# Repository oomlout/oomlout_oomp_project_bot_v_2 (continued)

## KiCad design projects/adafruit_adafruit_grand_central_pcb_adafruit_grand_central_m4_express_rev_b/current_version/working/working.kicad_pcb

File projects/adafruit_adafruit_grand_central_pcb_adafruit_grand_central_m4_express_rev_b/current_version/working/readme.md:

# adafruit_grand_central_pcb
 
## summary 
* id: adafruit_adafruit_grand_central_pcb_adafruit_grand_central_m4_express_rev_b
* user: adafruit
* name: adafruit_grand_central_pcb
* board: adafruit_grand_central_m4_express_rev_b
* repo: https://github.com/adafruit/Adafruit-Grand-Central-PCB

* src_file_repo_sch: 
* src_file_repo_sch_link: https://github.com/adafruit/Adafruit-Grand-Central-PCB/tree/master/
* full details link: https://github.com/oomlout/oomlout_oomp_project_bot_v_2/tree/main/projects/adafruit_adafruit_grand_central_pcb_adafruit_grand_central_m4_express_rev_b/current_version/working  

## schematic  
  
[schematic (pdf)](working_schematic.pdf) 

## pcb  

[board (pdf)](working.pdf)  

## bom_schematic
| Ref | Qnty | Value | Cmp name | Footprint | Description | Vendor | DNP | 
| --- | --- | --- | --- | --- | --- | --- | --- | 
| ANALOGH0 | 1 | 20610 | HEADER-1X8OVALWAVE | working:1X08_OVALWAVE |  |  |  | 
| ANALOGL0 | 1 | 20610 | HEADER-1X8OVALWAVE | working:1X08_OVALWAVE |  |  |  | 
| C1, C2, C3 | 3 | 10uF | CAP_CERAMIC0805-NOOUTLINE | working:0805-NO |  |  |  | 
| C4, C6, C8, C10, C11, C14, C15, C16, C18, C19, C20, C21, C22, C23, C24, C25 | 16 | .1u | CAP_CERAMIC0603_NO | working:0603-NO |  |  |  | 
| C5, C7 | 2 | 22pF | CAP_CERAMIC0603_NO | working:0603-NO |  |  |  | 
| C9 | 1 | 1uF | CAP_CERAMIC0603_NO | working:0603-NO |  |  |  | 
| C12, C13, C17 | 3 | 0.1uF | CAP_CERAMIC0603_NO | working:0603-NO |  |  |  | 
| D1 | 1 | MBR120 | DIODE-SCHOTTKYSOD-123 | working:SOD-123 |  |  |  | 
| F2 | 1 | 500mA | PTCFUSE-1206 | working:R1206 |  |  |  | 
| FB2 | 1 | FERRITE | FERRITE-0805NO | working:0805-NO |  |  |  | 
| FD1, FD2, FD3, FD4, FD5 | 5 | FIDUCIAL_1MM | FIDUCIAL_1MM | working:FIDUCIAL_1MM |  |  |  | 
| GROUND1 | 1 | SOLDERJUMPERCLOSED | SOLDERJUMPERCLOSED | working:SOLDERJUMPER_CLOSEDWIRE |  |  |  | 
| IC3 | 1 | 741G125DBV | 741G125DBV | working:SOT23-5 |  |  |  | 
| ICSP0 | 1 | 3x2 M | HEADER-2X3 | working:2X03_ROUND_70MIL |  |  |  | 
| IOH0 | 1 | 20611 | HEADER-1X10OVALWAVE | working:1X10_OVALWAVE |  |  |  | 
| IOL0 | 1 | 20610 | HEADER-1X8OVALWAVE | working:1X08_OVALWAVE |  |  |  | 
| JP1 | 1 | HEADER-1X1ROUND | HEADER-1X1ROUND | working:1X01_ROUND |  |  |  | 
| JP2 | 1 | PINHD-2X18_THICKWAV | PINHD-2X18_THICKWAV | working:2X18_THICKWAVE |  |  |  | 
| L0 | 1 | RED | LED0805_NOOUTLINE | working:CHIPLED_0805_NOOUTLINE |  |  |  | 
| L1 | 1 | 10uH | INDUCTOR | working:INDUCTOR_1007 |  |  |  | 
| LED1 | 1 | WS2812B3535 | WS2812B3535 | working:LED3535 |  |  |  | 
| ON0 | 1 | GREEN | LED0805_NOOUTLINE | working:CHIPLED_0805_NOOUTLINE |  |  |  | 
| PC1 | 1 | 47uF/25V | CAP_ELECTROLYTICPANASONIC_D | working:PANASONIC_D |  |  |  | 
| PC2 | 1 | 47uF+/6.3V+ | CAP_ELECTROLYTICPANASONIC_D | working:PANASONIC_D |  |  |  | 
| POWER0 | 1 | 20610 | HEADER-1X8OVALWAVE | working:1X08_OVALWAVE |  |  |  | 
| R1 | 1 | 100K | RESISTOR_4PACK | working:RESPACK_4X0603 |  |  |  | 
| R2 | 1 | 1K | RESISTOR_4PACK | working:RESPACK_4X0603 |  |  |  | 
| R3, R5, R7 | 3 | 10K | RESISTOR_0603_NOOUT | working:0603-NO |  |  |  | 
| R4 | 1 | 1K | RESISTOR_0603_NOOUT | working:0603-NO |  |  |  | 
| R11 | 1 | 330R | RESISTOR_0603_NOOUT | working:0603-NO |  |  |  | 
| RESET0 | 1 | EVQQ 6mm | SWITCH_TACT_SMT_EVQQ2_SMALL | working:EVQ-Q2_SMALLER |  |  |  | 
| RXLED0 | 1 | YELLOW | LED0805_NOOUTLINE | working:CHIPLED_0805_NOOUTLINE |  |  |  | 
| SJ1 | 1 | AREF_3V | SOLDERJUMPERCLOSED | working:SOLDERJUMPER_CLOSEDWIRE |  |  |  | 
| SW1 | 1 | SWITCH_SPDT | SWITCH_SPDT | working:SPDT_SMT_SSSS811101 |  |  |  | 
| T2 | 1 | DMP3098L-7 | PMOSSOT23 | working:SOT-23 |  |  |  | 
| TR1 | 1 | DMP3098L-7 | 0297_PMV48XP | working:SOT-23 |  |  |  | 
| TXLED0 | 1 | YELLOW | LED0805_NOOUTLINE | working:CHIPLED_0805_NOOUTLINE |  |  |  | 
| U1 | 1 | NCP1117ST50T3G | LM1117SOT223-REFLOW | working:SOT223-R |  |  |  | 
| U2 | 1 | LP2985-XXDBVR | LP2985-XXDBVR | working:SOT23-DBV |  |  |  | 
| U3 | 1 | GD25Q64 | SPIFLASH_SOIC8208MIL | working:SOIC8_208MIL |  |  |  | 
| U$1 | 1 | SAMD51PXXA | SAMD51PXXA | working:SQFP-S-14X14-128 |  |  |  | 
| UART0 | 1 | 20610 | HEADER-1X8OVALWAVE | working:1X08_OVALWAVE |  |  |  | 
| X1 | 1 | microsd | MICROSD | working:MICROSD |  |  |  | 
| X2 | 1 | 2x5 0.05" SWD | JTAG-CORTEXBOXPOSTS | working:2X05_1.27MM_BOX_POSTS |  |  |  | 
| X3 | 1 | USB_W_SHIELD_V2 | USB_W_SHIELD_V2 | working:4UCONN_20329_V2 |  |  |  | 
| X4 | 1 | 32.768 | XTAL-3.2X1.5 | working:XTAL3215 |  |  |  | 
| X5 | 1 | 2.1mm | DCBARRELPTH | working:DCJACK_2MM_PTH |  |  |  |

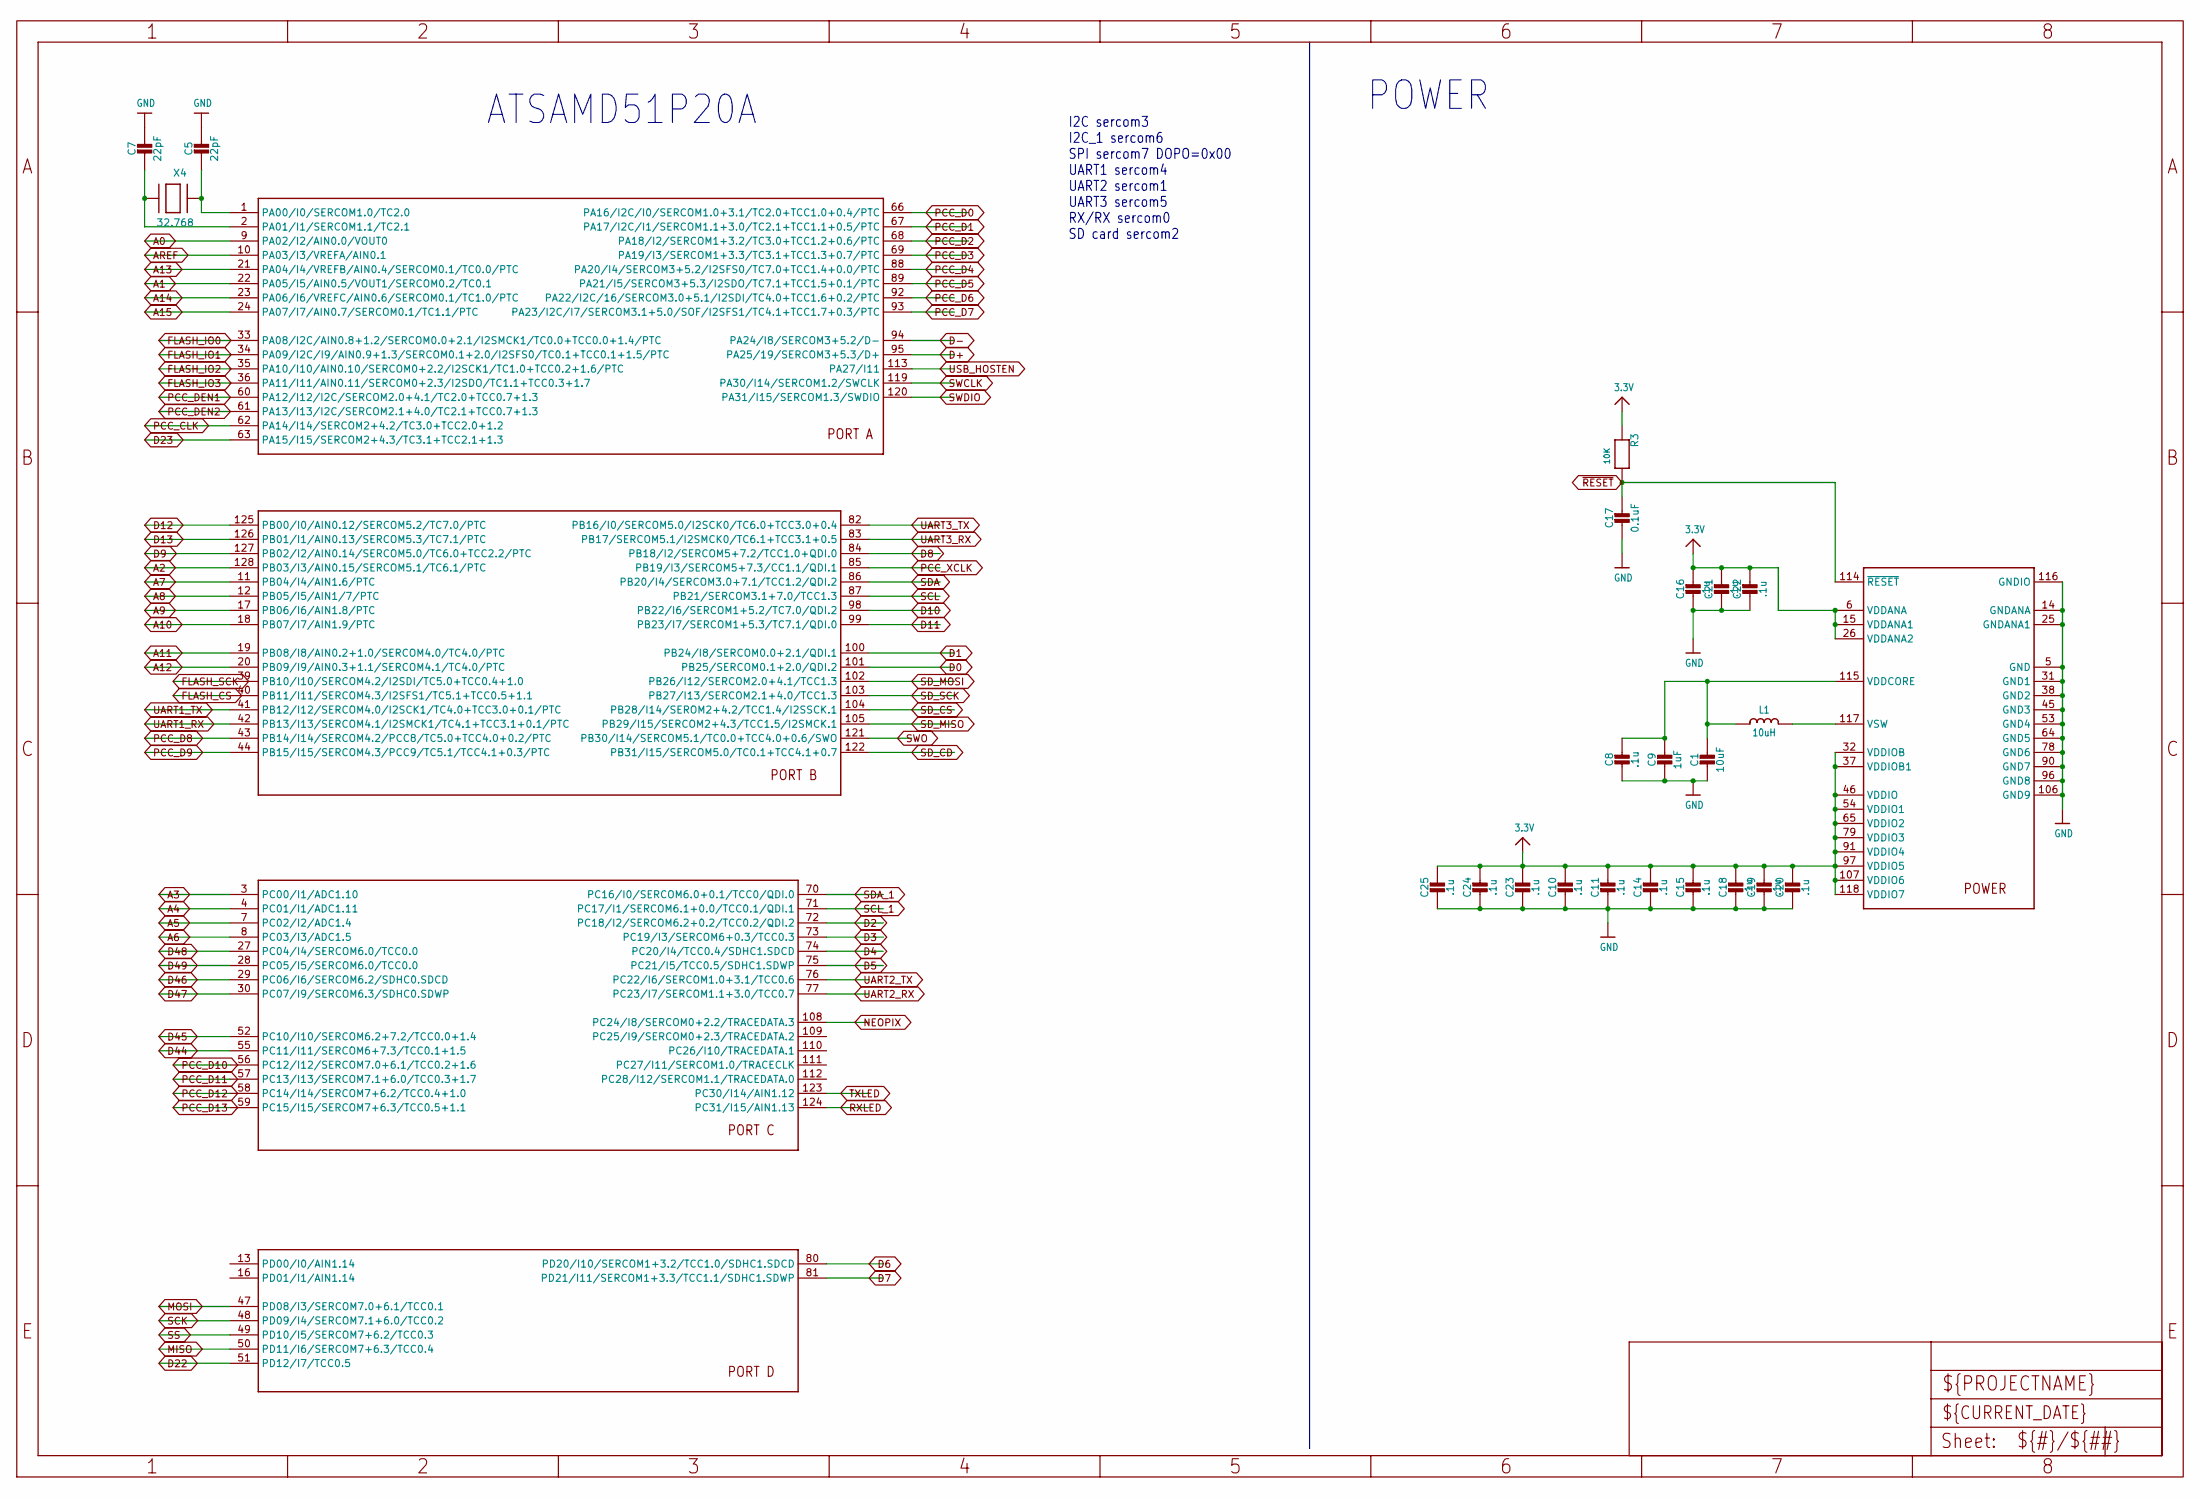
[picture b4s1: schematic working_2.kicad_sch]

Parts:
C1: 10uF; 0805-NO
C5, C7: 22pF; 0603-NO
C8, C10, C11, C14, C15, C16, C18, C19, C20, C21, C22, C23, C24, C25: .1u; 0603-NO
C9: 1uF; 0603-NO
C17: 0.1uF; 0603-NO
L1: 10uH; INDUCTOR_1007
R3: 10K; 0603-NO
U$1: SAMD51PXXA; SQFP-S-14X14-128
X4: 32.768; XTAL3215

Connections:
3.3V: C10.2, C11.2, C14.2, C15.2, C16.2, C18.2, C19.2, C20.2, C21.2, C22.2, C23.2, C24.2, C25.2, R3.1, U$1.6 (VDDANA), U$1.15 (VDDANA1), U$1.26 (VDDANA2), U$1.32 (VDDIOB), U$1.37 (VDDIOB1), U$1.46 (VDDIO), U$1.54 (VDDIO1), U$1.65 (VDDIO2), U$1.79 (VDDIO3), U$1.91 (VDDIO4), U$1.97 (VDDIO5), U$1.107 (VDDIO6), U$1.118 (VDDIO7); also elsewhere on the board
A0: U$1.9 (PA02/I2/AIN0.0/VOUT0); also elsewhere on the board
A1: U$1.22 (PA05/I5/AIN0.5/VOUT1/SERCOM0.2/TC0.1); also elsewhere on the board
A2: U$1.128 (PB03/I3/AIN0.15/SERCOM5.1/TC6.1/PTC); also elsewhere on the board
A3: U$1.3 (PC00/I1/ADC1.10); also elsewhere on the board
A4: U$1.4 (PC01/I1/ADC1.11); also elsewhere on the board
A5: U$1.7 (PC02/I2/ADC1.4); also elsewhere on the board
A6: U$1.8 (PC03/I3/ADC1.5); also elsewhere on the board
A7: U$1.11 (PB04/I4/AIN1.6/PTC); also elsewhere on the board
A8: U$1.12 (PB05/I5/AIN1/7/PTC); also elsewhere on the board
A9: U$1.17 (PB06/I6/AIN1.8/PTC); also elsewhere on the board
A10: U$1.18 (PB07/I7/AIN1.9/PTC); also elsewhere on the board
A11: U$1.19 (PB08/I8/AIN0.2+1.0/SERCOM4.0/TC4.0/PTC); also elsewhere on the board
A12: U$1.20 (PB09/I9/AIN0.3+1.1/SERCOM4.1/TC4.0/PTC); also elsewhere on the board
A13: U$1.21 (PA04/I4/VREFB/AIN0.4/SERCOM0.1/TC0.0/PTC); also elsewhere on the board
A14: U$1.23 (PA06/I6/VREFC/AIN0.6/SERCOM0.1/TC1.0/PTC); also elsewhere on the board
A15: U$1.24 (PA07/I7/AIN0.7/SERCOM0.1/TC1.1/PTC); also elsewhere on the board
AREF: U$1.10 (PA03/I3/VREFA/AIN0.1); also elsewhere on the board
D0: U$1.101 (PB25/SERCOM0.1+2.0/QDI.2); also elsewhere on the board
D1: U$1.100 (PB24/I8/SERCOM0.0+2.1/QDI.1); also elsewhere on the board
D2: U$1.72 (PC18/I2/SERCOM6.2+0.2/TCC0.2/QDI.2); also elsewhere on the board
D3: U$1.73 (PC19/I3/SERCOM6+0.3/TCC0.3); also elsewhere on the board
D4: U$1.74 (PC20/I4/TCC0.4/SDHC1.SDCD); also elsewhere on the board
D5: U$1.75 (PC21/I5/TCC0.5/SDHC1.SDWP); also elsewhere on the board
D6: U$1.80 (PD20/I10/SERCOM1+3.2/TCC1.0/SDHC1.SDCD); also elsewhere on the board
D7: U$1.81 (PD21/I11/SERCOM1+3.3/TCC1.1/SDHC1.SDWP); also elsewhere on the board
D8: U$1.84 (PB18/I2/SERCOM5+7.2/TCC1.0+QDI.0); also elsewhere on the board
D9: U$1.127 (PB02/I2/AIN0.14/SERCOM5.0/TC6.0+TCC2.2/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); also elsewhere on the board
D10: U$1.98 (PB22/I6/SERCOM1+5.2/TC7.0/QDI.2); also elsewhere on the board
D11: U$1.99 (PB23/I7/SERCOM1+5.3/TC7.1/QDI.0); also elsewhere on the board
D12: U$1.125 (PB00/I0/AIN0.12/SERCOM5.2/TC7.0/PTC); also elsewhere on the board
D13: U$1.126 (PB01/I1/AIN0.13/SERCOM5.3/TC7.1/PTC); also elsewhere on the board
D22: U$1.51 (PD12/I7/TCC0.5); also elsewhere on the board
D23: U$1.63 (PA15/I15/SERCOM2+4.3/TC3.1+TCC2.1+1.3); also elsewhere on the board
D44: U$1.55 (PC11/I11/SERCOM6+7.3/TCC0.1+1.5); also elsewhere on the board
D45: U$1.52 (PC10/I10/SERCOM6.2+7.2/TCC0.0+1.4); also elsewhere on the board
D46: U$1.29 (PC06/I6/SERCOM6.2/SDHC0.SDCD); also elsewhere on the board
D47: U$1.30 (PC07/I9/SERCOM6.3/SDHC0.SDWP); also elsewhere on the board
D48: U$1.27 (PC04/I4/SERCOM6.0/TCC0.0); also elsewhere on the board
D49: U$1.28 (PC05/I5/SERCOM6.0/TCC0.0); also elsewhere on the board
D+: U$1.95 (PA25/19/SERCOM3+5.3/D+); also elsewhere on the board
D-: U$1.94 (PA24/I8/SERCOM3+5.2/D-); also elsewhere on the board
FLASH_CS: U$1.40 (PB11/I11/SERCOM4.3/I2SFS1/TC5.1+TCC0.5+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); also elsewhere on the board
FLASH_IO0: U$1.33 (PA08/I2C/AIN0.8+1.2/SERCOM0.0+2.1/I2SMC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); also elsewhere on the board
FLASH_IO1: U$1.34 (PA09/I2C/I9/AIN0.9+1.3/SERCOM0.1+2.0/I2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); also elsewhere on the board
FLASH_IO2: U$1.35 (PA10/I10/AIN0.10/SERCOM0+2.2/I2SCK1/TC1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); also elsewhere on the board
FLASH_IO3: U$1.36 (PA11/I11/AIN0.11/SERCOM0+2.3/I2SDO/TC1.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); also elsewhere on the board
FLASH_SCK: U$1.39 (PB10/I10/SERCOM4.2/I2SDI/TC5.0+TCC0.4+1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); also elsewhere on the board
GND: C1.2, C5.2, C7.2, C8.1, C9.2, C10.1, C11.1, C14.1, C15.1, C16.1, C17.1, C18.1, C19.1, C20.1, C21.1, C22.1, C23.1, C24.1, C25.1, U$1.5 (GND), U$1.14 (GNDANA), U$1.25 (GNDANA1), U$1.31 (GND1), U$1.38 (GND2), U$1.45 (GND3), U$1.53 (GND4), U$1.64 (GND5), U$1.78 (GND6), U$1.90 (GND7), U$1.96 (GND8), U$1.106 (GND9), U$1.116 (GNDIO); also elsewhere on the board
MISO: U$1.50 (PD11/I6/SERCOM7+6.3/TCC0.4); also elsewhere on the board
MOSI: U$1.47 (PD08/I3/SERCOM7.0+6.1/TCC0.1); also elsewhere on the board
unnamed: L1.P$2 (2), U$1.117 (VSW)
unnamed: C5.1, U$1.1 (PA00/I0/SERCOM1.0/TC2.0), X4.P$1
unnamed: C7.1, U$1.2 (PA01/I1/SERCOM1.1/TC2.1), X4.P$2
NEOPIX: U$1.108 (PC24/I8/SERCOM0+2.2/TRACEDATA.3); also elsewhere on the board
PCC_CLK: U$1.62 (PA14/I14/SERCOM2+4.2/TC3.0+TCC2.0+1.2); also elsewhere on the board
PCC_D0: U$1.66 (PA16/I2C/I0/SERCOM1.0+3.1/TC2.0+TCC1.0+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); also elsewhere on the board
PCC_D1: U$1.67 (PA17/I2C/I1/SERCOM1.1+3.0/TC2.1+TCC1.1+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); also elsewhere on the board
PCC_D2: U$1.68 (PA18/I2/SERCOM1+3.2/TC3.0+TCC1.2+0.6/PTC); also elsewhere on the board
PCC_D3: U$1.69 (PA19/I3/SERCOM1+3.3/TC3.1+TCC1.3+0.7/PTC); also elsewhere on the board
PCC_D4: U$1.88 (PA20/I4/SERCOM3+5.2/I2SFS0/TC7.0+TCC1.4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); also elsewhere on the board
PCC_D5: U$1.89 (PA21/I5/SERCOM3+5.3/I2SDO/TC7.1+TCC1.5+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); also elsewhere on the board
PCC_D6: U$1.92 (PA22/I2C/16/SERCOM3.0+5.1/I2SDI/TC4.0+T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); also elsewhere on the board
PCC_D7: U$1.93 (PA23/I2C/I7/SERCOM3.1+5.0/SOF/I2SFS1/TC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); also elsewhere on the board
PCC_D8: U$1.43 (PB14/I14/SERCOM4.2/PCC8/TC5.0+TCC4.0+0.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); also elsewhere on the board
PCC_D9: U$1.44 (PB15/I15/SERCOM4.3/PCC9/TC5.1/TCC4.1+0.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); also elsewhere on the board
PCC_D10: U$1.56 (PC12/I12/SERCOM7.0+6.1/TCC0.2+1.6); also elsewhere on the board
PCC_D11: U$1.57 (PC13/I13/SERCOM7.1+6.0/TCC0.3+1.7); also elsewhere on the board
PCC_D12: U$1.58 (PC14/I14/SERCOM7+6.2/TCC0.4+1.0); also elsewhere on the board
PCC_D13: U$1.59 (PC15/I15/SERCOM7+6.3/TCC0.5+1.1); also elsewhere on the board
PCC_DEN1: U$1.60 (PA12/I12/I2C/SERCOM2.0+4.1/TC2.0+TCC0.7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); also elsewhere on the board
PCC_DEN2: U$1.61 (PA13/I13/I2C/SERCOM2.1+4.0/TC2.1+TCC0.7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); also elsewhere on the board
PCC_XCLK: U$1.85 (PB19/I3/SERCOM5+7.3/CC1.1/QDI.1); also elsewhere on the board
RXLED: U$1.124 (PC31/I15/AIN1.13); also elsewhere on the board
SCK: U$1.48 (PD09/I4/SERCOM7.1+6.0/TCC0.2); also elsewhere on the board
SCL: U$1.87 (PB21/SERCOM3.1+7.0/TCC1.3); also elsewhere on the board
SCL_1: U$1.71 (PC17/I1/SERCOM6.1+0.0/TCC0.1/QDI.1); also elsewhere on the board
SDA: U$1.86 (PB20/I4/SERCOM3.0+7.1/TCC1.2/QDI.2); also elsewhere on the board
SDA_1: U$1.70 (PC16/I0/SERCOM6.0+0.1/TCC0/QDI.0); also elsewhere on the board
SD_CD: U$1.122 (PB31/I15/SERCOM5.0/TC0.1+TCC4.1+0.7); also elsewhere on the board
SD_CS: U$1.104 (PB28/I14/SEROM2+4.2/TCC1.4/I2SSCK.1); also elsewhere on the board
SD_MISO: U$1.105 (PB29/I15/SERCOM2+4.3/TCC1.5/I2SMCK.1); also elsewhere on the board
SD_MOSI: U$1.102 (PB26/I12/SERCOM2.0+4.1/TCC1.3); also elsewhere on the board
SD_SCK: U$1.103 (PB27/I13/SERCOM2.1+4.0/TCC1.3); also elsewhere on the board
SS: U$1.49 (PD10/I5/SERCOM7+6.2/TCC0.3); also elsewhere on the board
SWCLK: U$1.119 (PA30/I14/SERCOM1.2/SWCLK); also elsewhere on the board
SWDIO: U$1.120 (PA31/I15/SERCOM1.3/SWDIO); also elsewhere on the board
SWO: U$1.121 (PB30/I14/SERCOM5.1/TC0.0+TCC4.0+0.6/SWO); also elsewhere on the board
TXLED: U$1.123 (PC30/I14/AIN1.12); also elsewhere on the board
UART1_RX: U$1.42 (PB13/I13/SERCOM4.1/I2SMCK1/TC4.1+TCC3.1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); also elsewhere on the board
UART1_TX: U$1.41 (PB12/I12/SERCOM4.0/I2SCK1/TC4.0+TCC3.0+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); also elsewhere on the board
UART2_RX: U$1.77 (PC23/I7/SERCOM1.1+3.0/TCC0.7); also elsewhere on the board
UART2_TX: U$1.76 (PC22/I6/SERCOM1.0+3.1/TCC0.6); also elsewhere on the board
UART3_RX: U$1.83 (PB17/SERCOM5.1/I2SMCK0/TC6.1+TCC3.1+0.5); also elsewhere on the board
UART3_TX: U$1.82 (PB16/I0/SERCOM5.0/I2SCK0/TC6.0+TCC3.0+0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); also elsewhere on the board
USB_HOSTEN: U$1.113 (PA27/I11); also elsewhere on the board
VDDCORE: C1.1, C8.2, C9.1, L1.P$1 (1), U$1.115 (VDDCORE)
~RESET: C17.2, R3.2, U$1.114 (~RESET); also elsewhere on the board

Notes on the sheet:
POWER
I2C sercom3 I2C_1 sercom6 SPI sercom7 DOPO=0x00 UART1 sercom4 UART2 sercom1 UART3 sercom5 RX/RX sercom0 SD card sercom2
ATSAMD51P20A

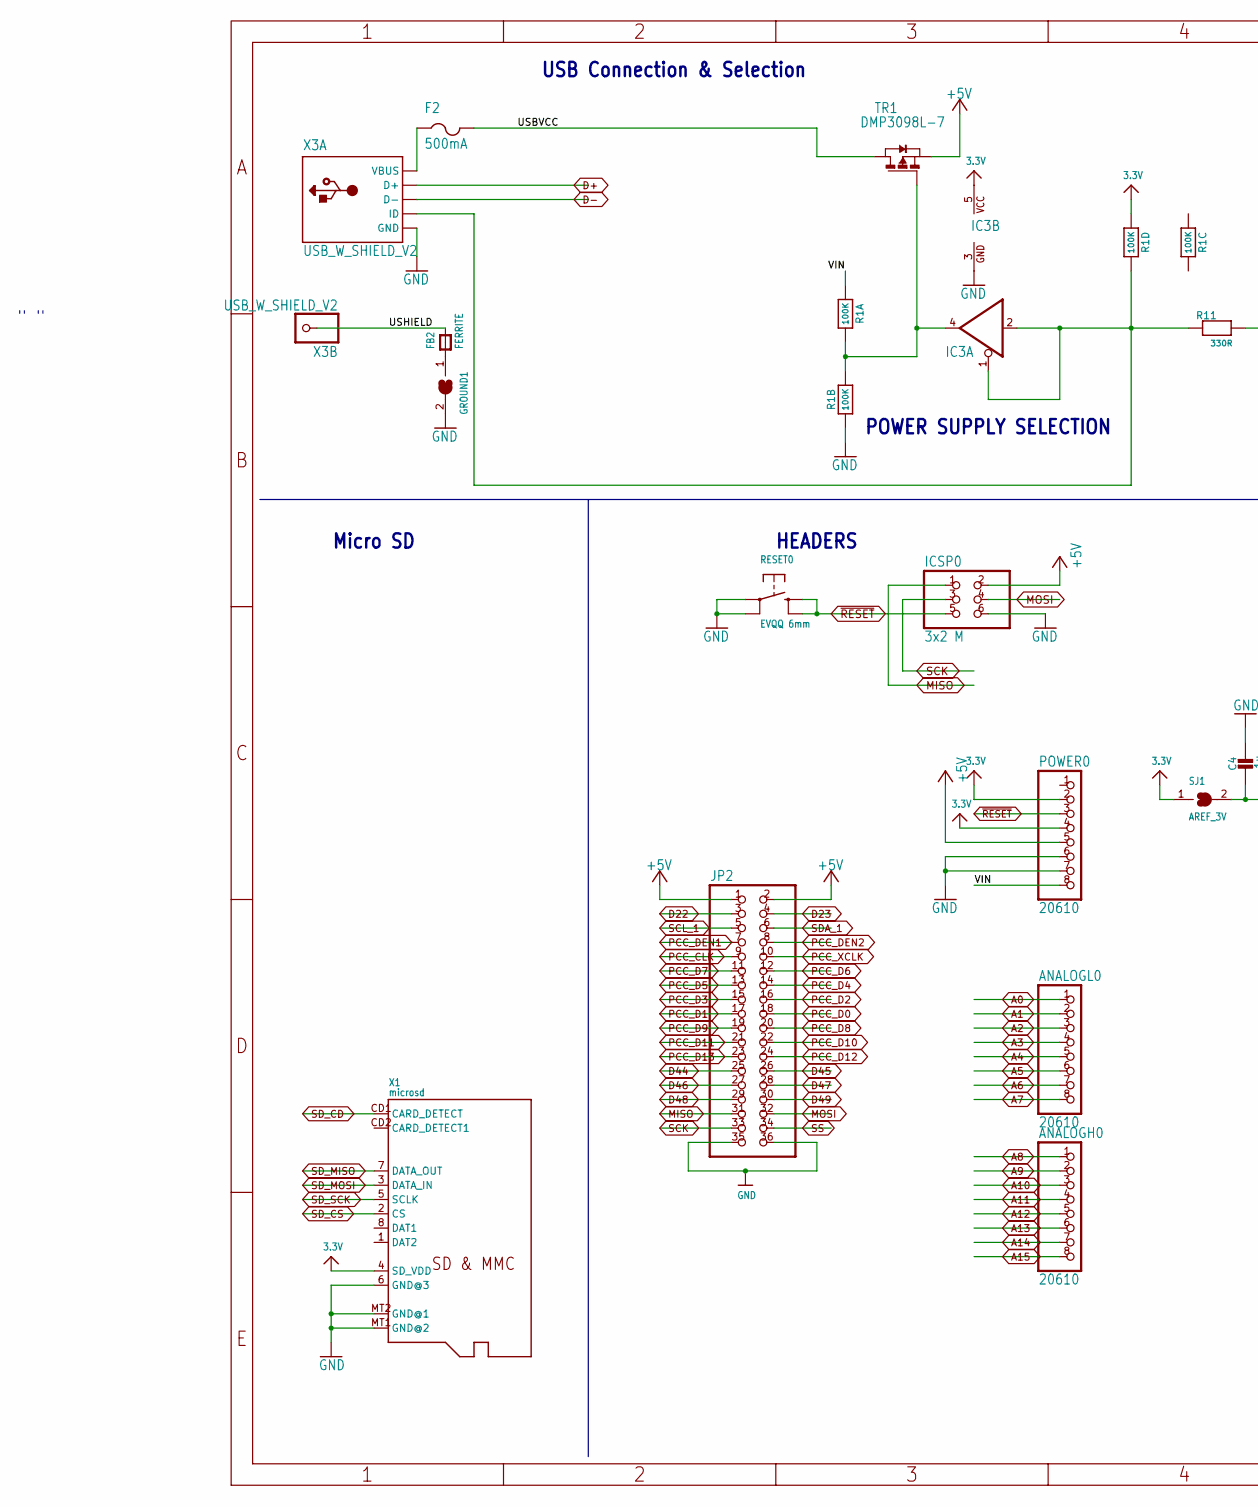
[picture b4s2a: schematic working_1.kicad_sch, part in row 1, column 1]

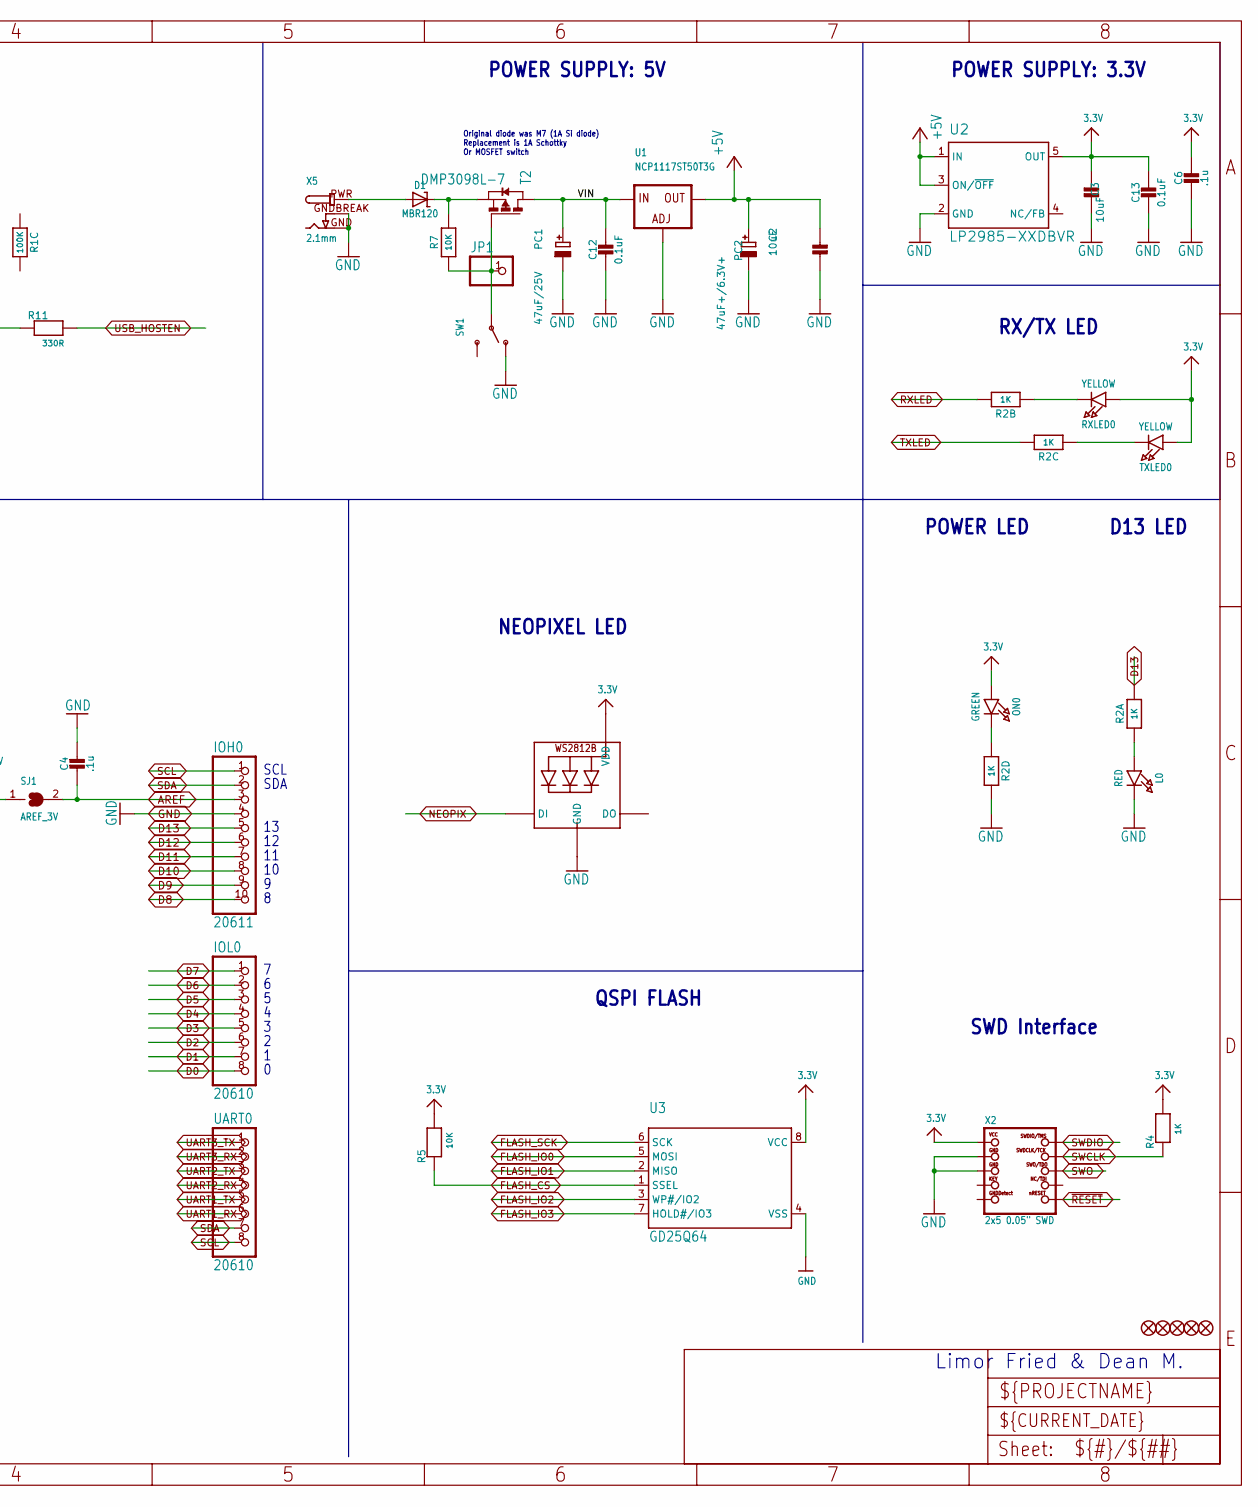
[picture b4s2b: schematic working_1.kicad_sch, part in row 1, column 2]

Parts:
ANALOGH0: 20610; 1X08_OVALWAVE
ANALOGL0: 20610; 1X08_OVALWAVE
C2, C3: 10uF; 0805-NO
C4, C6: .1u; 0603-NO
C12, C13: 0.1uF; 0603-NO
D1: MBR120; SOD-123
F2: 500mA; R1206
FB2: FERRITE; 0805-NO
FD1, FD2, FD3, FD4, FD5: FIDUCIAL_1MM
GROUND1: SOLDERJUMPERCLOSED; SOLDERJUMPER_CLOSEDWIRE
IC3: 741G125DBV; SOT23-5
ICSP0: 3x2 M; 2X03_ROUND_70MIL
IOH0: 20611; 1X10_OVALWAVE
IOL0: 20610; 1X08_OVALWAVE
JP1: HEADER-1X1ROUND; 1X01_ROUND
JP2: PINHD-2X18_THICKWAV; 2X18_THICKWAVE
L0: RED; CHIPLED_0805_NOOUTLINE
LED1: WS2812B3535; LED3535
ON0: GREEN; CHIPLED_0805_NOOUTLINE
PC1: 47uF/25V; PANASONIC_D
PC2: 47uF+/6.3V+; PANASONIC_D
POWER0: 20610; 1X08_OVALWAVE
R1: 100K; RESPACK_4X0603
R2: 1K; RESPACK_4X0603
R4: 1K; 0603-NO
R5, R7: 10K; 0603-NO
R11: 330R; 0603-NO
RESET0: EVQQ 6mm; EVQ-Q2_SMALLER
RXLED0: YELLOW; CHIPLED_0805_NOOUTLINE
SJ1: AREF_3V; SOLDERJUMPER_CLOSEDWIRE
SW1: SWITCH_SPDT; SPDT_SMT_SSSS811101
T2: DMP3098L-7; SOT-23
TR1: DMP3098L-7; SOT-23
TXLED0: YELLOW; CHIPLED_0805_NOOUTLINE
U1: NCP1117ST50T3G; SOT223-R
U2: LP2985-XXDBVR; SOT23-DBV
U3: GD25Q64; SOIC8_208MIL
UART0: 20610; 1X08_OVALWAVE
X1: microsd; MICROSD
X2: 2x5 0.05" SWD; 2X05_1.27MM_BOX_POSTS
X3: USB_W_SHIELD_V2; 4UCONN_20329_V2
X5: 2.1mm; DCJACK_2MM_PTH

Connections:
3.3V: C3.2, C6.2, C13.1, IC3.5 (VCC), LED1.2 (VDD), ON0.A, POWER0.2, POWER0.4, R1.4 (1), R4.2, R5.2, RXLED0.A, SJ1.1, TXLED0.A, U2.5 (OUT), U3.8 (VCC), X1.4 (SD_VDD), X2.1 (VCC); also elsewhere on the board
+5V: C2.2, ICSP0.2, JP2.1, JP2.2, PC2.+, POWER0.5, TR1.2 (S), U1.2 (OUT), U1.4 (OUT), U2.1 (IN), U2.3 (ON/~OFF)
A0: ANALOGL0.1; also elsewhere on the board
A1: ANALOGL0.2; also elsewhere on the board
A2: ANALOGL0.3; also elsewhere on the board
A3: ANALOGL0.4; also elsewhere on the board
A4: ANALOGL0.5; also elsewhere on the board
A5: ANALOGL0.6; also elsewhere on the board
A6: ANALOGL0.7; also elsewhere on the board
A7: ANALOGL0.8; also elsewhere on the board
A8: ANALOGH0.1; also elsewhere on the board
A9: ANALOGH0.2; also elsewhere on the board
A10: ANALOGH0.3; also elsewhere on the board
A11: ANALOGH0.4; also elsewhere on the board
A12: ANALOGH0.5; also elsewhere on the board
A13: ANALOGH0.6; also elsewhere on the board
A14: ANALOGH0.7; also elsewhere on the board
A15: ANALOGH0.8; also elsewhere on the board
AREF: C4.1, IOH0.3, SJ1.2; also elsewhere on the board
D0: IOL0.8; also elsewhere on the board
D1: IOL0.7; also elsewhere on the board
D2: IOL0.6; also elsewhere on the board
D3: IOL0.5; also elsewhere on the board
D4: IOL0.4; also elsewhere on the board
D5: IOL0.3; also elsewhere on the board
D6: IOL0.2; also elsewhere on the board
D7: IOL0.1; also elsewhere on the board
D8: IOH0.10; also elsewhere on the board
D9: IOH0.9; also elsewhere on the board
D10: IOH0.8; also elsewhere on the board
D11: IOH0.7; also elsewhere on the board
D12: IOH0.6; also elsewhere on the board
D13: IOH0.5, R2.8 (2); also elsewhere on the board
D22: JP2.3; also elsewhere on the board
D23: JP2.4; also elsewhere on the board
D44: JP2.25; also elsewhere on the board
D45: JP2.26; also elsewhere on the board
D46: JP2.27; also elsewhere on the board
D47: JP2.28; also elsewhere on the board
D48: JP2.29; also elsewhere on the board
D49: JP2.30; also elsewhere on the board
D+: X3.D+; also elsewhere on the board
D-: X3.D-; also elsewhere on the board
FLASH_CS: R5.1, U3.1 (SSEL); also elsewhere on the board
FLASH_IO0: U3.5 (MOSI); also elsewhere on the board
FLASH_IO1: U3.2 (MISO); also elsewhere on the board
FLASH_IO2: U3.3 (WP#/IO2); also elsewhere on the board
FLASH_IO3: U3.7 (HOLD#/IO3); also elsewhere on the board
FLASH_SCK: U3.6 (SCK); also elsewhere on the board
GND: C2.1, C3.1, C4.2, C6.1, C12.2, C13.2, GROUND1.2, IC3.3 (GND), ICSP0.6, IOH0.4, JP2.35, JP2.36, L0.C, LED1.4 (GND), PC1.-, PC2.-, POWER0.6, POWER0.7, R1.2 (1), R2.5 (2), RESET0.A, RESET0.A' (P1), SW1.A (O), U1.1 (ADJ), U2.2 (GND), U3.4 (VSS), X1.6 (GND@3), X1.MT1 (GND@2), X1.MT2 (GND@1), X2.3 (GND@1), X2.5 (GND@2), X3.GND, X5.GND, X5.GNDBREAK; also elsewhere on the board
MISO: ICSP0.1, JP2.31; also elsewhere on the board
MOSI: ICSP0.4, JP2.32; also elsewhere on the board
unnamed: L0.A, R2.1
unnamed: FB2.1, GROUND1.1
unnamed: ON0.C, R2.4 (1)
unnamed: R2.2 (1), RXLED0.C
unnamed: R2.3 (1), TXLED0.C
unnamed: IC3.1 (OE), IC3.2 (I), R1.5 (2), R11.1, X3.ID
unnamed: IC3.4 (O), R1.7 (2), R1.8 (2), TR1.3 (G)
unnamed: D1.C, R7.2, T2.2 (S)
NEOPIX: LED1.1 (DI); also elsewhere on the board
PCC_CLK: JP2.9; also elsewhere on the board
PCC_D0: JP2.18; also elsewhere on the board
PCC_D1: JP2.17; also elsewhere on the board
PCC_D2: JP2.16; also elsewhere on the board
PCC_D3: JP2.15; also elsewhere on the board
PCC_D4: JP2.14; also elsewhere on the board
PCC_D5: JP2.13; also elsewhere on the board
PCC_D6: JP2.12; also elsewhere on the board
PCC_D7: JP2.11; also elsewhere on the board
PCC_D8: JP2.20; also elsewhere on the board
PCC_D9: JP2.19; also elsewhere on the board
PCC_D10: JP2.22; also elsewhere on the board
PCC_D11: JP2.21; also elsewhere on the board
PCC_D12: JP2.24; also elsewhere on the board
PCC_D13: JP2.23; also elsewhere on the board
PCC_DEN1: JP2.7; also elsewhere on the board
PCC_DEN2: JP2.8; also elsewhere on the board
PCC_XCLK: JP2.10; also elsewhere on the board
PWRIN: D1.A, X5.PWR
PWR_SWITCH: JP1.1, R7.1, SW1.B, T2.3 (G)
RXLED: R2.7 (2); also elsewhere on the board
SCK: ICSP0.3, JP2.33; also elsewhere on the board
SCL: IOH0.1, UART0.8; also elsewhere on the board
SCL_1: JP2.5; also elsewhere on the board
SDA: IOH0.2, UART0.7; also elsewhere on the board
SDA_1: JP2.6; also elsewhere on the board
SD_CD: X1.CD1 (CARD_DETECT); also elsewhere on the board
SD_CS: X1.2 (CS); also elsewhere on the board
SD_MISO: X1.7 (DATA_OUT); also elsewhere on the board
SD_MOSI: X1.3 (DATA_IN); also elsewhere on the board
SD_SCK: X1.5 (SCLK); also elsewhere on the board
SS: JP2.34; also elsewhere on the board
SWCLK: R4.1, X2.4 (SWDCLK); also elsewhere on the board
SWDIO: X2.2 (SWDIO); also elsewhere on the board
SWO: X2.6 (SWO); also elsewhere on the board
TXLED: R2.6 (2); also elsewhere on the board
UART1_RX: UART0.6; also elsewhere on the board
UART1_TX: UART0.5; also elsewhere on the board
UART2_RX: UART0.4; also elsewhere on the board
UART2_TX: UART0.3; also elsewhere on the board
UART3_RX: UART0.2; also elsewhere on the board
UART3_TX: UART0.1; also elsewhere on the board
USBVCC: F2.2, TR1.1 (D)
USB_HOSTEN: R11.2; also elsewhere on the board
USHIELD: FB2.2, X3.BASE@1 (1), X3.BASE@2 (1), X3.SPRT@1 (1), X3.SPRT@2 (1), X3.SPRT@3 (1), X3.SPRT@4 (1)
VBUS: F2.1, X3.VBUS
VIN: C12.1, PC1.+, POWER0.8, R1.1, T2.1 (D), U1.3 (IN)
~RESET: ICSP0.5, POWER0.3, RESET0.B (S), RESET0.B' (S1), X2.10 (NRESET); also elsewhere on the board

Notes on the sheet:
HEADERS
POWER SUPPLY: 3.3V
POWER SUPPLY SELECTION
Limor Fried & Dean M.
QSPI FLASH
D13 LED
NEOPIXEL LED
Micro SD
USB Connection & Selection
Original diode was M7 (1A Si diode) Replacement is 1A Schottky Or MOSFET switch
POWER LED
" "
POWER SUPPLY: 5V
SCL
RX/TX LED
SWD Interface
SDA

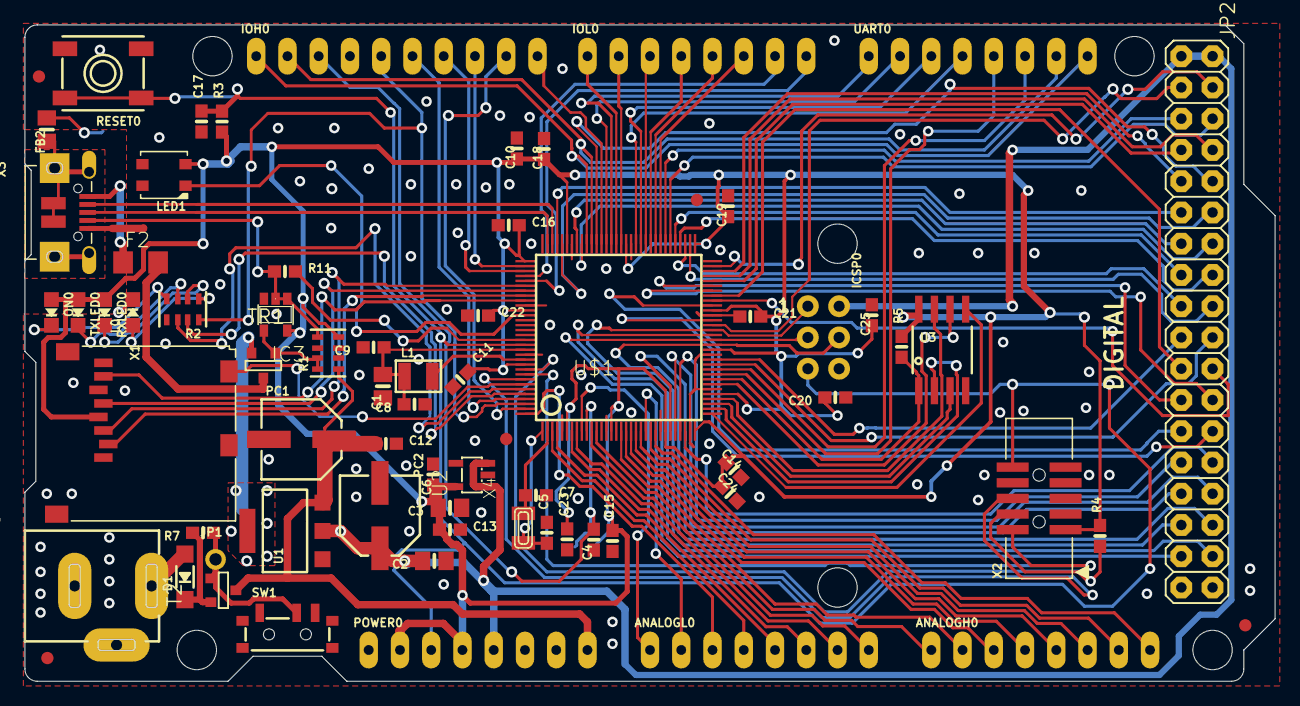
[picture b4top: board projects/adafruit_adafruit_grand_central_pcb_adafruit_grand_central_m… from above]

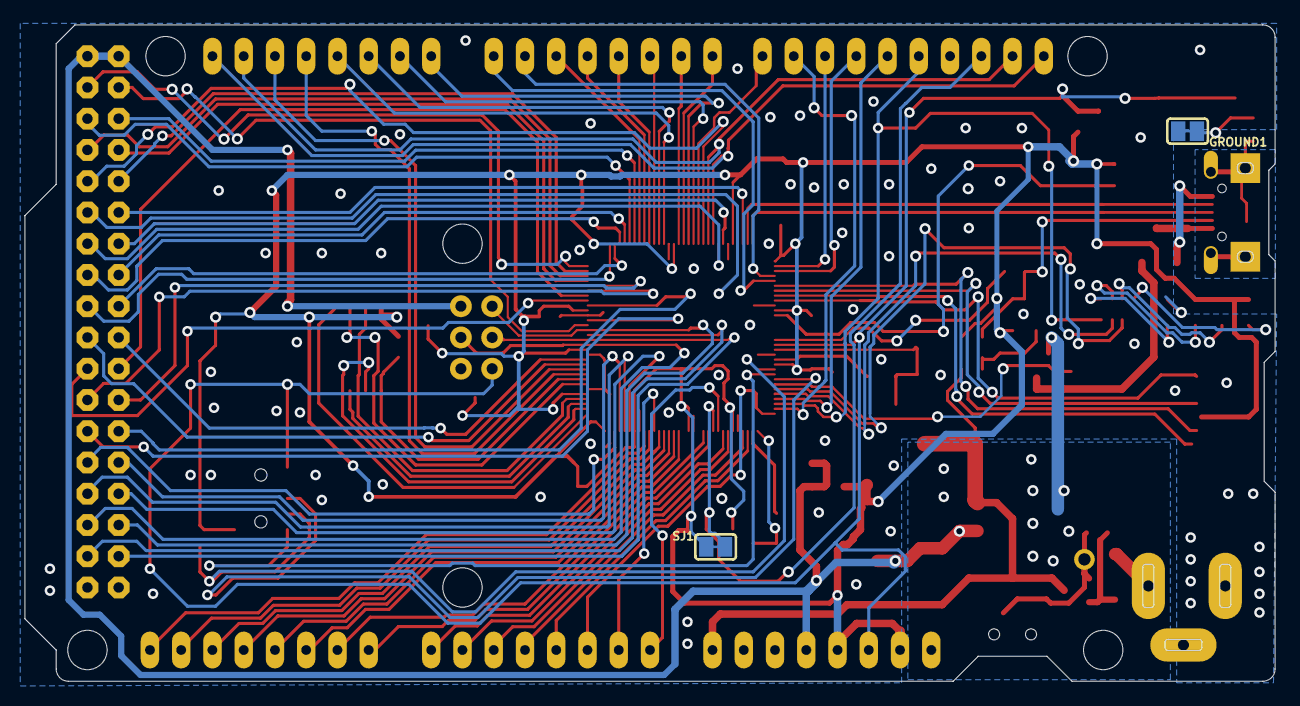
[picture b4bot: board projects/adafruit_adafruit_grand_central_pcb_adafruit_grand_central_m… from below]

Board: 2 copper layers, 101.6 x 53.3 mm, 81 parts (3 on the bottom side), 113 nets.

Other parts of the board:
@HOLE0, @HOLE1, @HOLE2, @HOLE3, @HOLE4, @HOLE5: (no value)
U$23: GRANDCENTRAL_REVB-BOT
U$30: GRANDCENTRAL_REVB_TOP

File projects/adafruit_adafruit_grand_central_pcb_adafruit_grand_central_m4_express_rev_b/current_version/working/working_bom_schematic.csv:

"Source:","C:\gh\oomlout_oomp_project_bot_v_2\projects\adafruit_adafruit_grand_central_pcb_adafruit_grand_central_m4_express_rev_b\current_version\working\working.kicad_sch"
"Date:","14/09/2023 06:57:10"
"Tool:","Eeschema 7.0.6"
"Generator:","C:/Program Files/KiCad/7.0/bin/scripting/plugins/bom_csv_grouped_by_value_with_fp.py"
"Component Count:","73"
"Ref","Qnty","Value","Cmp name","Footprint","Description","Vendor","DNP"
"ANALOGH0","1","20610","HEADER-1X8OVALWAVE","working:1X08_OVALWAVE","","",""
"ANALOGL0","1","20610","HEADER-1X8OVALWAVE","working:1X08_OVALWAVE","","",""
"C1, C2, C3","3","10uF","CAP_CERAMIC0805-NOOUTLINE","working:0805-NO","","",""
"C4, C6, C8, C10, C11, C14, C15, C16, C18, C19, C20, C21, C22, C23, C24, C25","16",".1u","CAP_CERAMIC0603_NO","working:0603-NO","","",""
"C5, C7","2","22pF","CAP_CERAMIC0603_NO","working:0603-NO","","",""
"C9","1","1uF","CAP_CERAMIC0603_NO","working:0603-NO","","",""
"C12, C13, C17","3","0.1uF","CAP_CERAMIC0603_NO","working:0603-NO","","",""
"D1","1","MBR120","DIODE-SCHOTTKYSOD-123","working:SOD-123","","",""
"F2","1","500mA","PTCFUSE-1206","working:R1206","","",""
"FB2","1","FERRITE","FERRITE-0805NO","working:0805-NO","","",""
"FD1, FD2, FD3, FD4, FD5","5","FIDUCIAL_1MM","FIDUCIAL_1MM","working:FIDUCIAL_1MM","","",""
"GROUND1","1","SOLDERJUMPERCLOSED","SOLDERJUMPERCLOSED","working:SOLDERJUMPER_CLOSEDWIRE","","",""
"IC3","1","741G125DBV","741G125DBV","working:SOT23-5","","",""
"ICSP0","1","3x2 M","HEADER-2X3","working:2X03_ROUND_70MIL","","",""
"IOH0","1","20611","HEADER-1X10OVALWAVE","working:1X10_OVALWAVE","","",""
"IOL0","1","20610","HEADER-1X8OVALWAVE","working:1X08_OVALWAVE","","",""
"JP1","1","HEADER-1X1ROUND","HEADER-1X1ROUND","working:1X01_ROUND","","",""
"JP2","1","PINHD-2X18_THICKWAV","PINHD-2X18_THICKWAV","working:2X18_THICKWAVE","","",""
"L0","1","RED","LED0805_NOOUTLINE","working:CHIPLED_0805_NOOUTLINE","","",""
"L1","1","10uH","INDUCTOR","working:INDUCTOR_1007","","",""
"LED1","1","WS2812B3535","WS2812B3535","working:LED3535","","",""
"ON0","1","GREEN","LED0805_NOOUTLINE","working:CHIPLED_0805_NOOUTLINE","","",""
"PC1","1","47uF/25V","CAP_ELECTROLYTICPANASONIC_D","working:PANASONIC_D","","",""
"PC2","1","47uF+/6.3V+","CAP_ELECTROLYTICPANASONIC_D","working:PANASONIC_D","","",""
"POWER0","1","20610","HEADER-1X8OVALWAVE","working:1X08_OVALWAVE","","",""
"R1","1","100K","RESISTOR_4PACK","working:RESPACK_4X0603","","",""
"R2","1","1K","RESISTOR_4PACK","working:RESPACK_4X0603","","",""
"R3, R5, R7","3","10K","RESISTOR_0603_NOOUT","working:0603-NO","","",""
"R4","1","1K","RESISTOR_0603_NOOUT","working:0603-NO","","",""
"R11","1","330R","RESISTOR_0603_NOOUT","working:0603-NO","","",""
"RESET0","1","EVQQ 6mm","SWITCH_TACT_SMT_EVQQ2_SMALL","working:EVQ-Q2_SMALLER","","",""
"RXLED0","1","YELLOW","LED0805_NOOUTLINE","working:CHIPLED_0805_NOOUTLINE","","",""
"SJ1","1","AREF_3V","SOLDERJUMPERCLOSED","working:SOLDERJUMPER_CLOSEDWIRE","","",""
"SW1","1","SWITCH_SPDT","SWITCH_SPDT","working:SPDT_SMT_SSSS811101","","",""
"T2","1","DMP3098L-7","PMOSSOT23","working:SOT-23","","",""
"TR1","1","DMP3098L-7","0297_PMV48XP","working:SOT-23","","",""
"TXLED0","1","YELLOW","LED0805_NOOUTLINE","working:CHIPLED_0805_NOOUTLINE","","",""
"U1","1","NCP1117ST50T3G","LM1117SOT223-REFLOW","working:SOT223-R","","",""
"U2","1","LP2985-XXDBVR","LP2985-XXDBVR","working:SOT23-DBV","","",""
"U3","1","GD25Q64","SPIFLASH_SOIC8208MIL","working:SOIC8_208MIL","","",""
"U$1","1","SAMD51PXXA","SAMD51PXXA","working:SQFP-S-14X14-128","","",""
"UART0","1","20610","HEADER-1X8OVALWAVE","working:1X08_OVALWAVE","","",""
"X1","1","microsd","MICROSD","working:MICROSD","","",""
"X2","1","2x5 0.05"" SWD","JTAG-CORTEXBOXPOSTS","working:2X05_1.27MM_BOX_POSTS","","",""
"X3","1","USB_W_SHIELD_V2","USB_W_SHIELD_V2","working:4UCONN_20329_V2","","",""
"X4","1","32.768","XTAL-3.2X1.5","working:XTAL3215","","",""
"X5","1","2.1mm","DCBARRELPTH","working:DCJACK_2MM_PTH","","",""
